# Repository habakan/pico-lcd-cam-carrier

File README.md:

# pico-lcd-cam-carrier

A carrier board and case for building [SeedSigner on the Raspberry Pi Pico 2](https://github.com/habakan/seedsigner-pico)
without soldering. A Raspberry Pi Pico 2 H, a Waveshare 1.3inch LCD HAT (240x240 ST7789, a joystick and three
keys) and an OV7675 camera (Arducam B0070) plug into it. KiCad files, the scripts that generate them, and 3D
print files for the case.

> [!NOTE]
> **Rev E is tested on an assembled board.** The screen, the camera, all eight buttons and the firmware's
> self-test work with [seedsigner-pico](https://github.com/habakan/seedsigner-pico)'s `main`. When soldering
> the connectors yourself, check every pin of the HAT's header (J3): one dry joint there left the screen blank
> while its backlight still lit.

[日本語の README](README.ja.md) · [BOM with prices](BOM.md)

| Directory | Revision | How it goes together |
|---|---|---|
| [hat-carrier/](hat-carrier/README.md) | Rev E | Everything plugs into sockets; no soldering. Tested |
| [pico2h-carrier/](pico2h-carrier/README.md) | Rev D | A draft where the LCD, the Pico and the camera are soldered on |

## Rev E

| Front (HAT side) | Back (Pico and camera side) |
|---|---|
|  |  |

The front takes the HAT on a 2x20 male header (J3). The back has two 1x20 sockets for the Pico (J1, J2) and a
2x10 socket for the camera (J4).

| Front | Back |
|---|---|
|  |  |

The parts in these renders are boxes of the right size, not the real models.

The case's front cover follows SeedSigner's [Orange Pill](https://github.com/SeedSigner/seedsigner/tree/dev/enclosures/orange_pill)
(MIT), so its joystick and key caps fit. About 91 x 39 x 36 mm.

## Pin map

This table is the contract with the firmware. Change the firmware's pin definitions with it.

| Function | Pico GPIO |
|---|---|
| Camera D0-D7 | GP2-GP9 (PIO reads them as one run, so keep the order) |
| Camera PCLK / HREF / VSYNC | GP10 / GP11 / GP12 |
| Camera SIOD / SIOC (I2C1) | GP14 / GP15 |
| Camera XCLK (GPOUT0) | GP21 |
| LCD DC / SCK / MOSI (SPI0) | GP16 / GP18 / GP19 |
| LCD RST | GP0 |
| LCD CS | tied to GND (SPI mode 3) |
| Joystick up / down / left / right / press | GP13 / GP17 / GP20 / GP22 / GP26 |
| Keys A / B / C | GP27 / GP28 / GP1 |

Buttons pull to GND when pressed, against the RP2350's internal pull-ups.

## Origin

Split, with its history, from `hardware/kicad/` in
[bitwasm-signer-pico](https://github.com/bitwasm-project/bitwasm-signer-pico). The case's front cover and caps
come from SeedSigner's Orange Pill (MIT, `hat-carrier/3dprint/seedsigner/LICENSE.md`).

## License

MIT ([LICENSE](LICENSE)). The Orange Pill parts in `hat-carrier/3dprint/seedsigner/` keep SeedSigner's MIT license.

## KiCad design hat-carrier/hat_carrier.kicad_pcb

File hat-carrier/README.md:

# HAT carrier (KiCad draft, Rev E)

A draft carrier board for building a Waveshare 1.3inch LCD HAT, a Pico 2 H and an OV7675 (Arducam B0070) **by plugging them in, without soldering**. The board is ordered with its four connectors already fitted, so the builder only plugs in three boards and tightens the screws. It is a separate line from [Rev D](../pico2h-carrier/README.md), which is assembled by soldering.

The GPIO assignment matches `src/board_pins.h` in bitwasm-signer-pico (the table in the [README](../README.md)).

## Files

- `generate.py`: writes the four files below. To change the wiring or the placement, edit it and run `python3 generate.py`.
- `route.py`: run after `generate.py` with the Python bundled with KiCad. It places J1–J4, assigns the nets, autoroutes on two layers and pours GND on both sides.
  `~/Applications/KiCad/KiCad.app/Contents/Frameworks/Python.framework/Versions/Current/bin/python3 route.py`
- `hat_carrier.kicad_sch`: schematic at the connector level.
- `HatCarrier.kicad_sym` / `sym-lib-table`: symbols for this design.
- `hat_carrier.kicad_pcb`: 86 x 34 mm outline with 1 mm chamfers at the corners, three M2.5 holes for the HAT and four M2 holes for the case, mechanical areas for the parts and pin rows (Dwgs.User), J1–J4 and the tracks. Do not edit it by hand; regenerate it from the two scripts.
- `3dprint/`: case generation script and print files. [3dprint/README.md](3dprint/README.md)

## Connectors

| Ref | For | Side | Footprint |
|---|---|---|---|
| J1 | Pico 2 H left row, physical pins 1–20 | B | 1x20 2.54 mm pin socket |
| J2 | Pico 2 H right row, physical pins 40–21 from the USB end | B | 1x20 2.54 mm pin socket |
| J3 | 1.3inch LCD HAT (Raspberry Pi 40-pin numbering) | F | 2x20 2.54 mm pin header (male) |
| J4 | OV7675 / Arducam B0070 | B | 2x10 2.54 mm pin socket (pad numbers use the pin header footprint) |

At J4's position, seen from the front, the pin numbers are mirrored left to right against how KiCad numbers its socket, so the numbering is matched by using the pin header footprint with the same pad layout. Checked with the real camera (2026-11-07). Seen from the pin side with the header at the top, pin 1 is the left end of the top row (the board-edge side).

The HAT-side connections were checked against Waveshare's schematic (`1.3inch-LCD-HAT-Schematic.pdf`).

| J3 pin | HAT signal | Net | Pico |
|---|---|---|---|
| 1, 17 | 3.3V | 3V3 | physical 36 |
| 13 | LCD RST | LCD_RES (the firmware resets it at boot, as in seedsigner-pico) | GP0 |
| 18 | LCD BL | 3V3 (also pulled up with 10k on the HAT) | - |
| 24 | LCD CS | GND (SPI mode 3) | - |
| 6, 9, 14, 20, 25, 30, 34, 39 | GND | GND | - |
| 23 / 19 / 22 | LCD CLK / DIN / DC | LCD_SCK / LCD_MOSI / LCD_DC | GP18 / GP19 / GP16 |
| 31 / 35 / 29 / 37 / 33 | up / down / left / right / press | BTN_UP / DOWN / LEFT / RIGHT / SELECT | GP13 / GP17 / GP20 / GP22 / GP26 |
| 40 / 38 / 36 | KEY1 / KEY2 / KEY3 | BTN_REJECT / BTN_B / BTN_C | GP27 / GP28 / GP1 |
| 2, 4 | 5V | **not connected** | - |

The camera is connected as in Rev D, with PEN tied to 3V3 and PDN tied to GND. Buttons pull to GND when pressed, and use the RP2350's internal pull-ups.

## Placement

PCB coordinates (KiCad coordinates seen from the front, mm). B-side parts are placed mirrored left to right as seen from the front.

| Part | Side | Position | Orientation |
|---|---|---|---|
| HAT | F | (10.5, 0.5)–(75.5, 30.7) | Joystick on the left, LCD in the center, KEY1–3 on the right. Socket on the bottom edge |
| J3 | F | center (43, 27.2) | Pin 1 is at the right end of the top (inner) row (67.13, 25.93) |
| Pico 2 H | B | (0.75, 12.25)–(51.75, 33.25) | Component side faces the back, USB on the left edge |
| J1 / J2 | B | rows y = 13.86 / 31.64, x = 2.12–50.38 | Both have pin 1 at the USB end (left) |
| B0070 | B | (54.75, 1.75)–(85.25, 32.25) | Lens faces the back, center (69.99, 19.60). Header on the top edge (upside down from Rev D) |
| J4 | B | rows y = 3.02 (odd) / 5.56 (even), x = 58.56–81.42 | Pin 1 at the left end |
| H1–H3 | - | (14, 4.0), (14, 27.2), (72, 27.2) | Coaxial with the HAT's mounting holes. M2.5 x 10 mm female-female spacers support the HAT (as in SeedSigner's Orange Pill) |
| H4–H7 | - | (2.75, 17.05), (2.75, 28.45), (81.505, 28.52), (81.505, 11.02) | Coaxial with the mounting holes of the Pico and the camera. The case's M2 screws pass through them |

- The HAT's top-right mounting hole (72, 4.0) has no hole in the carrier, because a screw head there would overlap the camera socket on the back. The front cover's post holds that corner.
- The camera is upside down from Rev D because with the header on the bottom edge, J4 would overlap J3. The image can be rotated 180° with the OV7675's MVFP register (0x1E). The current firmware does not set this register, so decide after assembly by checking the preview orientation.
- The screw heads of H1–H3 (Ø4.5) sit under the Pico and the camera. Both are raised by the socket and header plastic (11 mm), so they do not touch, but tighten the screws before plugging in the Pico and the camera. The gap between H2's screw head and J2's socket is 0.9 mm, and the spacing between the pins of J3 and J2 is 3.3 mm.
- The Pico's SWD connector at the right end is only 3 mm from the camera. To use SWD, open the case and unplug the camera.

## Stack-up (from the back, estimated)

| z (mm) | Part |
|---|---|
| 0–2.4 | Back case |
| 3.0–6.5 | Camera lens (the Pico's USB and SWD are 2.9 mm, lower than this) |
| 6.5–8.1 | Camera board |
| 8.1–19.1 | Camera header plastic 2.5 + socket 8.5 |
| 19.1–20.7 | Carrier board |
| 20.7–30.7 | J3 plastic 2.5 + HAT socket 7.5 |
| 30.7–32.3 | HAT board |
| 32.3–34.0 | LCD module (1.7 mm or less) |
| 32.3–36.3 | Front cover (rests directly on the HAT board, recessed only at the parts) |

The case is expected to be about **91.4 x 39.4 x 36.3 mm**. With low-profile sockets of about 5 mm for J1, J2 and J4, it gets down to about 32.8 mm. Most of the thickness is the two levels of sockets, and the 10 mm on the HAT side is set by the HAT's socket, so it cannot be reduced.

## Source of the HAT dimensions

No 3D CAD data is published. The values below come from the [dimension drawing](https://www.waveshare.com/img/devkit/LCD/1.3inch-LCD-HAT/1.3inch-LCD-HAT-size.jpg) and product photos on Waveshare's product page, and from the STLs of SeedSigner's [Orange Pill case](https://github.com/SeedSigner/seedsigner/tree/dev/enclosures/orange_pill) (MIT), which uses the same HAT. Coordinates within the HAT have their origin at the top left, seen from the LCD side with the joystick on the left.

| Item | Value | Basis |
|---|---|---|
| Outline | 65 x 30.2, corner R1.5 | Dimension drawing |
| Mounting holes | (3.5, 3.5), (61.5, 3.5), (3.5, 26.7), (61.5, 26.7), M2.5 | Spacing 58 x 23.2 in the dimension drawing |
| Socket | Bottom edge, center (32.5, 26.7), pin 1 at the inner side of the right end | Photos (underside, mounted on a Pi Zero and a Pi 3) and the Pi HAT spec |
| LCD glass | (17.7, 1.85)–(47.2, 28.35) | Measured to scale from the dimension drawing image, ±0.3 mm |
| Joystick center | (7.16, 15.45) | Center of the Orange Pill hole. The dimension drawing reads (6.1, 15.2), but the hole was matched because the Orange Pill caps are used |
| KEY1 / KEY2 / KEY3 centers | (57.1, 9.2) / (57.1, 15.2) / (57.1, 21.1) | Same as above. Also matches the Orange Pill key holes (57.0, spacing 5.9) |
| LCD active area center | (31.25, 15.35) | Center of the Orange Pill window (24 x 24.5). About 1 mm toward the joystick from the glass center |
| LCD height | 1.7 mm or less | Depth of the Orange Pill's recess for the glass |
| Joystick and key height | Not measured | The front cover has the same shape as the Orange Pill and uses its caps ([3dprint/README.md](3dprint/README.md)) |
| Socket height | About 7.5 mm | The Orange Pill fixes the Pi Zero and the HAT with 10 mm spacers. This is that minus the 2.5 mm header plastic on the Pi side |

## To measure on the real parts

| Item | Current assumption | Used for |
|---|---|---|
| Socket height, HAT board thickness | 7.5 / 1.6 mm | Thickness. Checking the estimate above |
| Height of parts on the HAT's underside | Unknown | Interference around J3 |

## Routing

Maze routing on `route.py`'s grid (0.1 mm). Track width 0.25 mm, clearance 0.15 mm and vias 0.6/0.3 mm, which fit JLCPCB's standard process. One track passes between pads at 2.54 mm pitch.

- No copper within a 3.0 mm radius of the HAT's M2.5 holes (spacers and screw heads), within a 2.3 mm radius of the case's M2 holes, or within 0.5 mm of the board edge.
- Signals are routed shortest first, and 3V3 and GND last. GND is also connected through the pours on both sides.
- The current result is 28 nets, 7 vias, 0 unrouted.

## Next steps

1. Measure the items in "To measure on the real parts", fix the constants in `generate.py` and rerun the two scripts.
2. Test-print the case (`3dprint/`) and check that the Orange Pill caps move.
3. Get a quote for ordering the board with the connectors fitted. Also check here whether low-profile sockets can be chosen.

## Checks

Checked with `kicad-cli` from KiCad 10.0.7.

- Schematic ERC has 0 errors. The only warnings are 4 saying the footprint library is not registered in the CLI environment.
- In the exported netlist, the pins of each net match the table above and `board_pins.h`. 3V3 has 6 pins, GND has 18 pins, and every signal, including LCD_RES, has 2 pins.
- PCB DRC has 0 violations and 0 unconnected items. The remaining findings are warnings that the mounting hole library is not registered (one per hole) and too few thermal relief spokes on two GND pads (both are connected to GND by tracks).

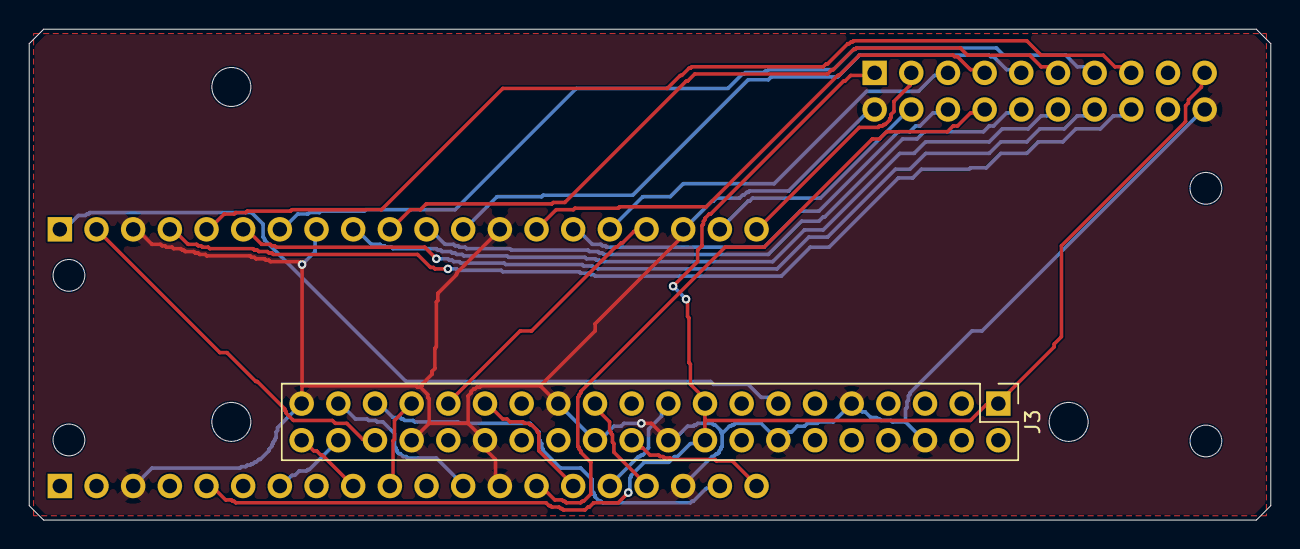
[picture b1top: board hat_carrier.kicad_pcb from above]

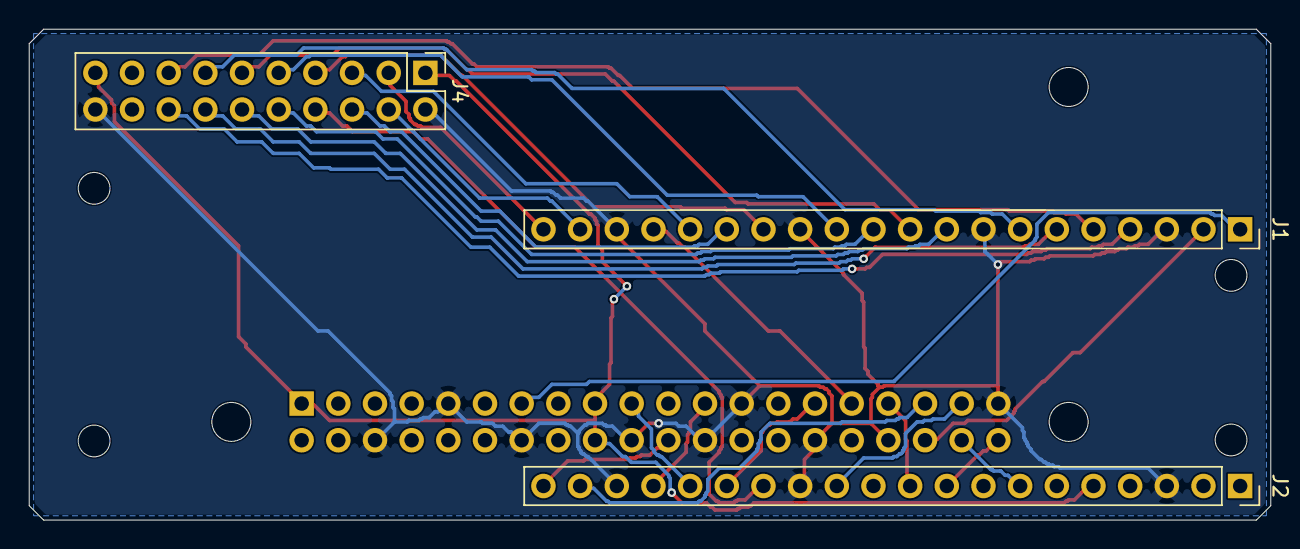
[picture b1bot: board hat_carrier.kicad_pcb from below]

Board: 2 copper layers, 86.0 x 34.0 mm, 11 parts (3 on the bottom side), 28 nets.

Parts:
H1, H2, H3: MountingHole_2.7mm_M2.5
H4, H5, H6, H7: MountingHole_2.2mm_M2
J1, J2: PinSocket_1x20_P2.54mm_Vertical
J3: PinHeader_2x20_P2.54mm_Vertical
J4: PinHeader_2x10_P2.54mm_Vertical

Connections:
3V3: J2.5, J3.1, J3.17, J3.18, J4.1, J4.19
BTN_B: J2.7, J3.38
BTN_C: J1.2, J3.36
BTN_DOWN: J2.19, J3.35
BTN_LEFT: J2.15, J3.29
BTN_REJECT: J2.9, J3.40
BTN_RIGHT: J2.12, J3.37
BTN_SELECT: J2.10, J3.33
BTN_UP: J1.17, J3.31
CAM_D0: J1.4, J4.16
CAM_D1: J1.5, J4.15
CAM_D2: J1.6, J4.14
CAM_D3: J1.7, J4.13
CAM_D4: J1.9, J4.12
CAM_D5: J1.10, J4.11
CAM_D6: J1.11, J4.10
CAM_D7: J1.12, J4.9
CAM_HREF: J1.15, J4.6
CAM_PCLK: J1.14, J4.7
CAM_SCL: J1.20, J4.3
CAM_SDA: J1.19, J4.4
CAM_VSYNC: J1.16, J4.5
CAM_XCLK: J2.14, J4.8
GND: J1.3, J1.8, J1.13, J1.18, J2.3, J2.13, J2.18, J3.6, J3.9, J3.14, J3.20, J3.24, J3.25, J3.30, J3.34, J3.39, J4.2, J4.20
LCD_DC: J2.20, J3.22
LCD_MOSI: J2.16, J3.19
LCD_RES: J1.1, J3.13
LCD_SCK: J2.17, J3.23
